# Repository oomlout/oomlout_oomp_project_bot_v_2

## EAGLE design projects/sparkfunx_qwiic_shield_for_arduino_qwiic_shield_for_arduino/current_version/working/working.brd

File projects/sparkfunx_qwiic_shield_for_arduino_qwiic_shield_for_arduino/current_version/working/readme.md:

# qwiic_shield_for_arduino
 
## summary 
* id: sparkfunx_qwiic_shield_for_arduino_qwiic_shield_for_arduino
* user: sparkfunx
* name: qwiic_shield_for_arduino
* board: qwiic_shield_for_arduino
* repo: https://github.com/sparkfunX/Qwiic_Shield_for_Arduino

* src_file_repo_sch: 
* src_file_repo_sch_link: https://github.com/sparkfunX/Qwiic_Shield_for_Arduino/tree/master/
* full details link: https://github.com/oomlout/oomlout_oomp_project_bot_v_2/tree/main/projects/sparkfunx_qwiic_shield_for_arduino_qwiic_shield_for_arduino/current_version/working

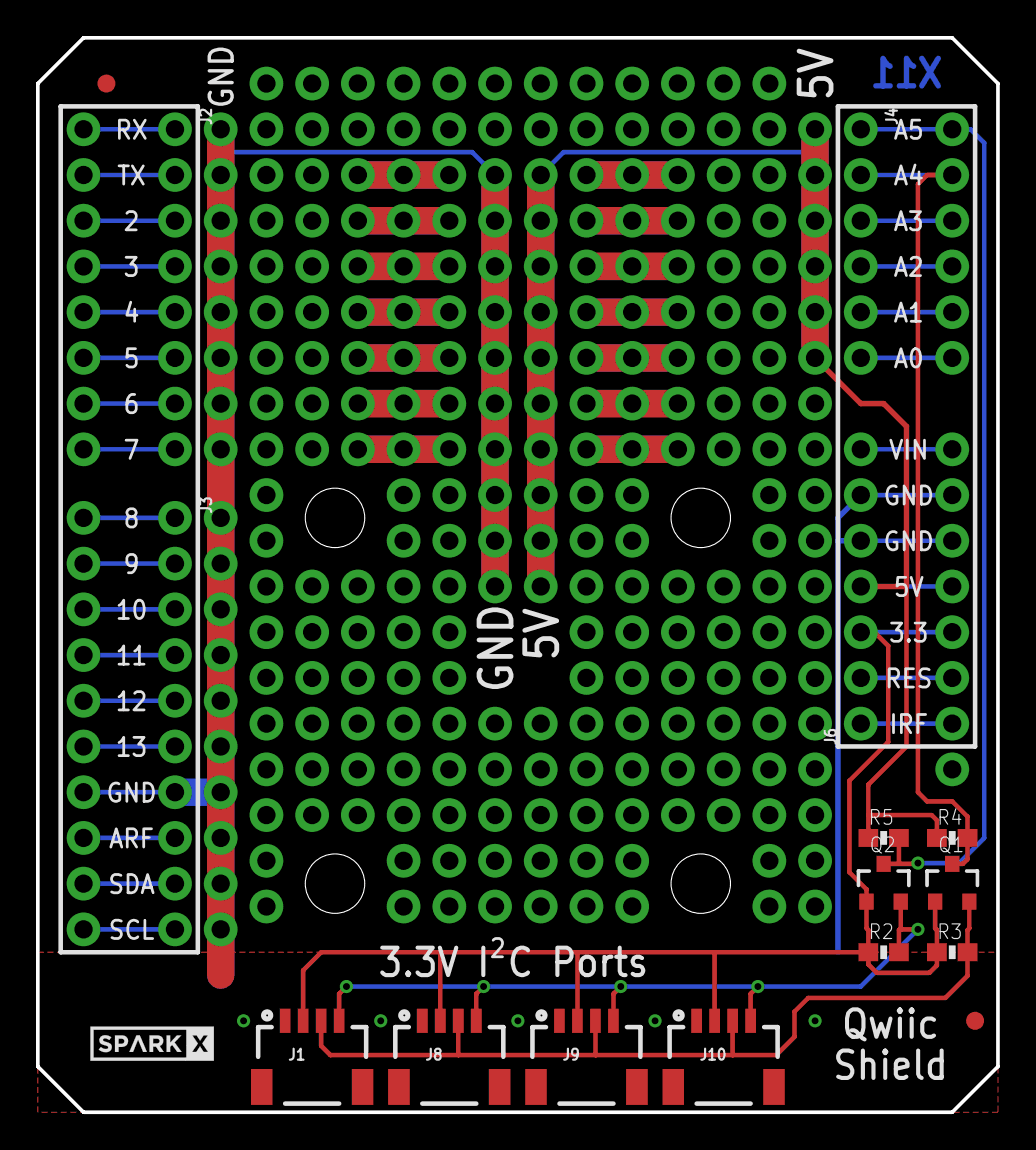
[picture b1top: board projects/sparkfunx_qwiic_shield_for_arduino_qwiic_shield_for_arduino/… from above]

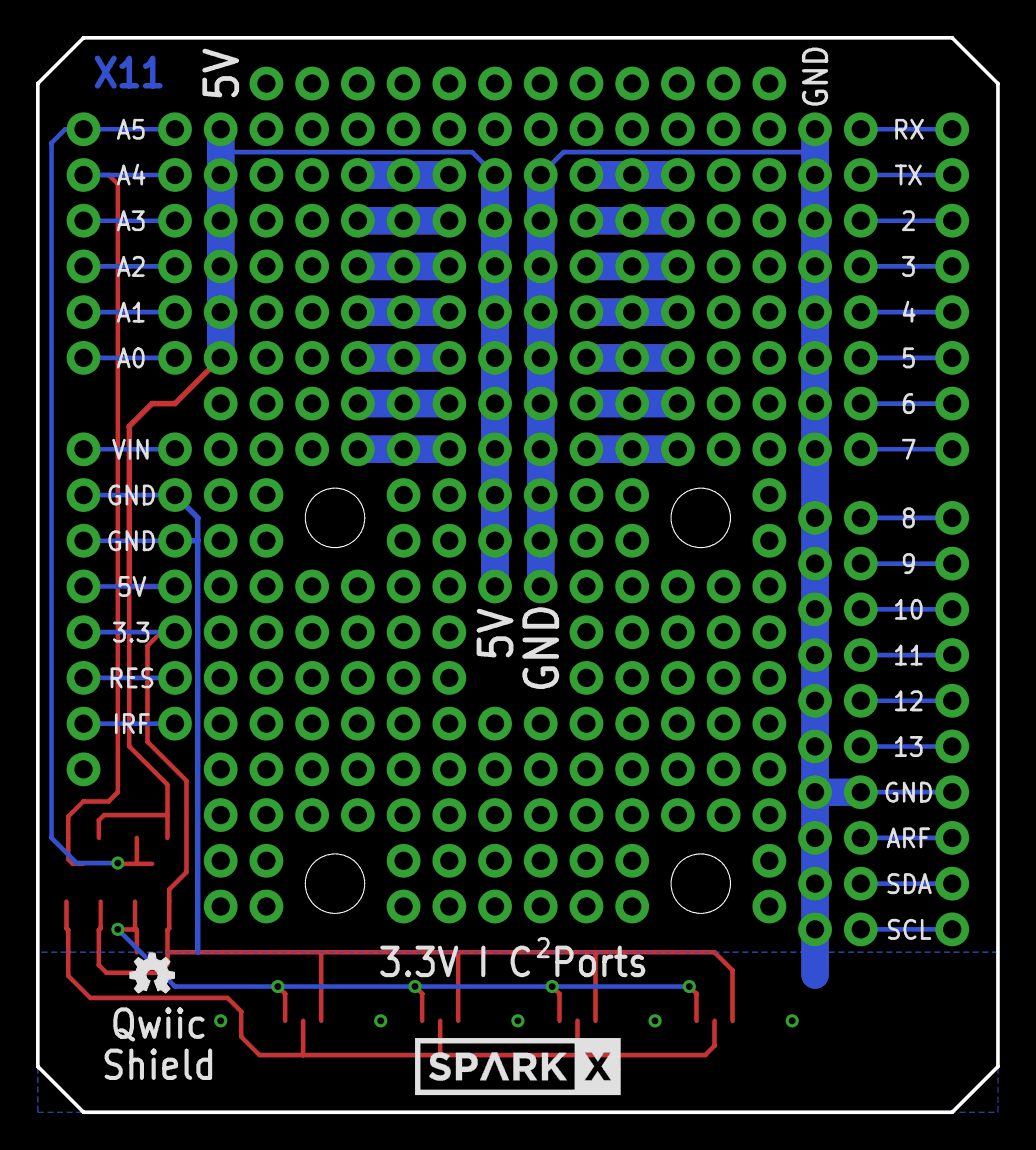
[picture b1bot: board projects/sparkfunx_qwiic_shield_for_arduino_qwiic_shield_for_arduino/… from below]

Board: 2 copper layers, 53.3 x 59.7 mm, 22 parts (2 on the bottom side), 31 nets.

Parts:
FD1, FD2: FIDUCIAL1X2; FIDUCIAL-1X2
FRAME1: FRAME-LETTER; CREATIVE_COMMONS
J1, J8, J9, J10: 1X04_1MM_RA
J2: 1X08_NO_SILK
J3: 1X10_NO_SILK
J4: 1X06_NO_SILK
J6: 1X07_NO_SILK
LOGO1: OSHW-LOGOMINI; OSHW-LOGO-MINI
Q1, Q2: BSS138; SOT23-3
R2, R3, R4, R5: 4.7K; 0603-RES
U1: ARDUINO UNO; UNO_R3_SHIELD_NOLABELS
U$1: SPARKX-LOGO3; SPARKX-SMALL
U$2: SPARKX-LOGO5; SPARKX-LARGE
U$3: QWIIC_BOARD_OUTLINEH; QWIIC_BOARD_MOUNT_HOLES

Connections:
3.3V: J1.2, J6.3, J8.2, J9.2, J10.2, Q1.1, Q2.1, R2.1, R3.1, U1.3.3V
5V: J6.4, R4.1, R5.1, U1.5V
A0: J4.6, U1.A0
A1: J4.5, U1.A1
A2: J4.4, U1.A2
A3: J4.3, U1.A3
AREF: J3.8, U1.AREF
D2: J2.3, U1.D2
D3: J2.4, U1.D3
D4: J2.5, U1.D4
D5: J2.6, U1.D5
D6: J2.7, U1.D6
D7: J2.8, U1.D7
D8: J3.1, U1.D8
D9: J3.2, U1.D9
D10: J3.3, U1.D10
D11: J3.4, U1.D11
D12: J3.5, U1.D12
D13: J3.6, U1.D13
GND: J1.1, J3.7, J6.5, J6.6, J8.1, J9.1, J10.1, U1.GND@0, U1.GND@1, U1.GND@2
HV_SCL: J4.1, Q2.3, R5.2, U1.A5
HV_SDA: J4.2, Q1.3, R4.2, U1.A4
IOREF: J6.1, U1.IOREF
RES: J6.2, U1.RES
RX: J2.1, U1.RX
SCL: J1.4, J8.4, J9.4, J10.4, Q2.2, R2.2
SCL1: J3.10, U1.SCL
SDA: J1.3, J8.3, J9.3, J10.3, Q1.2, R3.2
SDA1: J3.9, U1.SDA
TX: J2.2, U1.TX
VIN: J6.7, U1.VIN

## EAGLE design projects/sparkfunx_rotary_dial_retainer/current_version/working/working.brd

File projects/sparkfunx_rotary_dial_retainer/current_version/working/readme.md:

# rotary_dial
 
## summary 
* id: sparkfunx_rotary_dial_retainer
* user: sparkfunx
* name: rotary_dial
* board: retainer
* repo: https://github.com/sparkfunX/Rotary_Dial

* src_file_repo_sch: 
* src_file_repo_sch_link: https://github.com/sparkfunX/Rotary_Dial/tree/master/
* full details link: https://github.com/oomlout/oomlout_oomp_project_bot_v_2/tree/main/projects/sparkfunx_rotary_dial_retainer/current_version/working

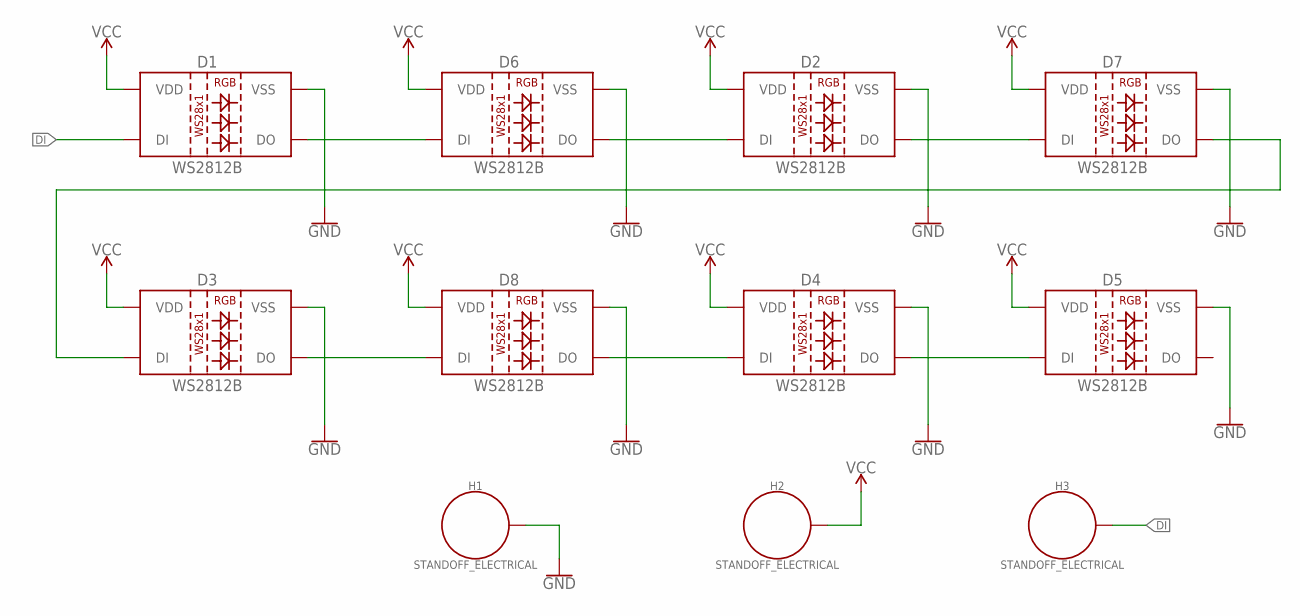
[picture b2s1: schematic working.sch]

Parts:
D1, D2, D3, D4, D5, D6, D7, D8: WS2812B
H1, H2, H3: STANDOFF_ELECTRICAL; STANDOFF-ELECTRICAL

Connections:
DI: D1.4 (DI), H3.P1
GND: D1.3 (VSS), D2.3 (VSS), D3.3 (VSS), D4.3 (VSS), D5.3 (VSS), D6.3 (VSS), D7.3 (VSS), D8.3 (VSS), H1.P1
unnamed: D1.2 (DO), D6.4 (DI)
unnamed: D2.4 (DI), D6.2 (DO)
unnamed: D2.2 (DO), D7.4 (DI)
unnamed: D3.4 (DI), D7.2 (DO)
unnamed: D3.2 (DO), D8.4 (DI)
unnamed: D4.4 (DI), D8.2 (DO)
unnamed: D4.2 (DO), D5.4 (DI)
VCC: D1.1 (VDD), D2.1 (VDD), D3.1 (VDD), D4.1 (VDD), D5.1 (VDD), D6.1 (VDD), D7.1 (VDD), D8.1 (VDD), H2.P1

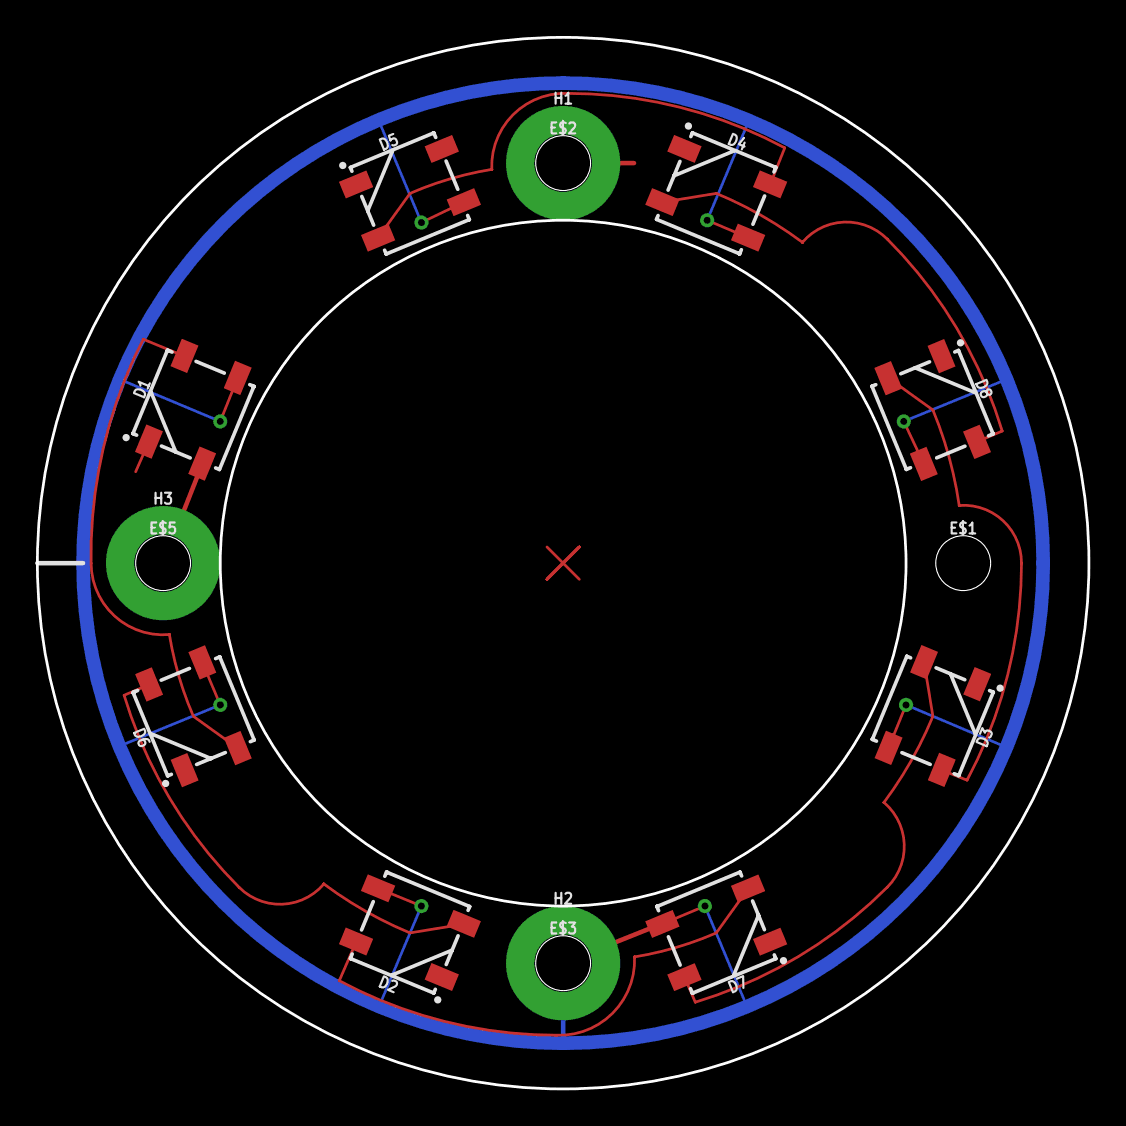
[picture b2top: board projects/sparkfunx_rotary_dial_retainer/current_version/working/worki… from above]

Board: 2 copper layers, 58.4 x 58.4 mm, 15 parts (0 on the bottom side), 10 nets.

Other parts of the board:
E$1, E$2, E$3, E$5: STAND-OFF-TIGHT

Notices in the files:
parts and their libraries:
SparkFun-Boards: Licensing: CC v3.0 Share-Alike You are welcome to use this library for commercial purposes.
SparkFun-Aesthetics: Released under the Creative Commons Attribution Share-Alike 4.0 License
SparkFun-Aesthetics: https://creativecommons.org/licenses/by-sa/4.0
